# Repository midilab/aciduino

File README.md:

# Aciduino

The DIY Arduino-based Roland TB303 and TR808 Step Sequencer clone and MIDI Controller. Designed using readily available, inexpensive parts. It can be easily assembled on a protoboard or [ordered as PCB](https://pushermanproductions.com/product/midilab-aciduino-303-style-midi-sequencer-pcb-only/). 

There are two flavors of aciduino, the [first version(v1)](https://github.com/midilab/aciduino/tree/master/v1/) is a TB303 sequencer only, the [second version(v2)](https://github.com/midilab/aciduino/tree/master/v2/) is a TB303 and TR808 sequencer with oled display and step/pattern/mute grid system.

Find out more about at [official home page](https://midilab.co/aciduino/)

## [Aciduino V1](https://github.com/midilab/aciduino/tree/master/v1/)  
2 Tracks TB303 sequencer and MIDI Controller.

V1 on PCB

## [Aciduino V2](https://github.com/midilab/aciduino/tree/master/v2/)  
Up to 16 Tracks TB303/TR808 sequencer with step, pattern and mute automation grid system, MIDI Controller, OLED display and extensible modular design to plug more potentiometers, buttons, MIDI or CV/Gate interfaces.

V2 on Protoboard

V2 on PCB(prototype)

Features
========

### 303/808 Step Sequencer clone

Programming bass and drum steps using same analogy of original machines • Save your pattern work on microcontroller EPPROM memory for later live gigs • Use step length and shift to make some unusual sequences • Automation grid system for step edit, pattern navigation and mute tracks • Realtime and Step record modes for MIDI keyboard input(v2 only)

### Professional grade Clock

Tight and solid clock system using hardware timers to achieve realtime professional grade tick system • Send or receive clock to keep all your external equipment synced

### Generative Engine

Generate new and fresh acid music patterns by pressing a single button and twist some parameters • Harmonizer to force musical harmonic modes for bass lines • Euclidian generator for drum parts

### Midi Controller

Controls up to 16 parameters per track of your external synthesizers(bass/drums) • Midi learn(v2 only) • 16 potentiometers modular support to extend aciduino as midi controller(v2 only)

### Pattern memory

Store your patterns conveniently on the microcontroller's EEPROM, allowing you to access them effortlessly during live performances.

# Easy and fast Assembly

1 or 2 hours assembly time on protoboard. 

[V1 Assembly](https://github.com/midilab/aciduino/tree/master/v1)

[V2 Assembly](https://github.com/midilab/aciduino/tree/master/v2#assembly)

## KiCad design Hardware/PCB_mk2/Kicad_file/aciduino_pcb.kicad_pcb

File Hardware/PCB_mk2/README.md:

# ACIDUINO PCB MK2
### <span style="color: red; ">ACIDUINO has been upgraded to MK2 with MIDIinput!</span>
I have created a PCB that can build an aciduino by midilab as a bare board device.
It would be easy to build with less number parts!
Please refer to the folder hierarchy above for the code.
(Be sure to use the latest firmware!)

↓↓↓Completed build image↓↓↓

# About Fabrication
You can get the PCB by submitting the "aciduino_gerber.zip" to a PCB fabrication company in China.
It's usually a lot of 5 pieces.

# BOM List

* 1x arduino nano
* 10x 220ohms resistors
* 1x 4.7kohms resistors
* 1x 1N4148 diodes
* 1x 6N138 optocoupler
* 6x Key switches(If you don't like that, you can substitute a 6mm taticle switch)
* 6x 3mm diffused leds
* 4x 10k linear potentiometers
* 2xMIDI Connector[like this](http://modularanalog.com/?product=midi-jack-5-pin-din-pcb-mount)

!! Additional !!
- A hole is provided to connect a 9V battery box.
- It also works with power supplied from the Arduino's USB port.
- DEMO with my modular and polyend traker(use as MIDI master)[instagram](https://www.instagram.com/reel/CaJfxwNDVI4/?utm_source=ig_web_copy_link)

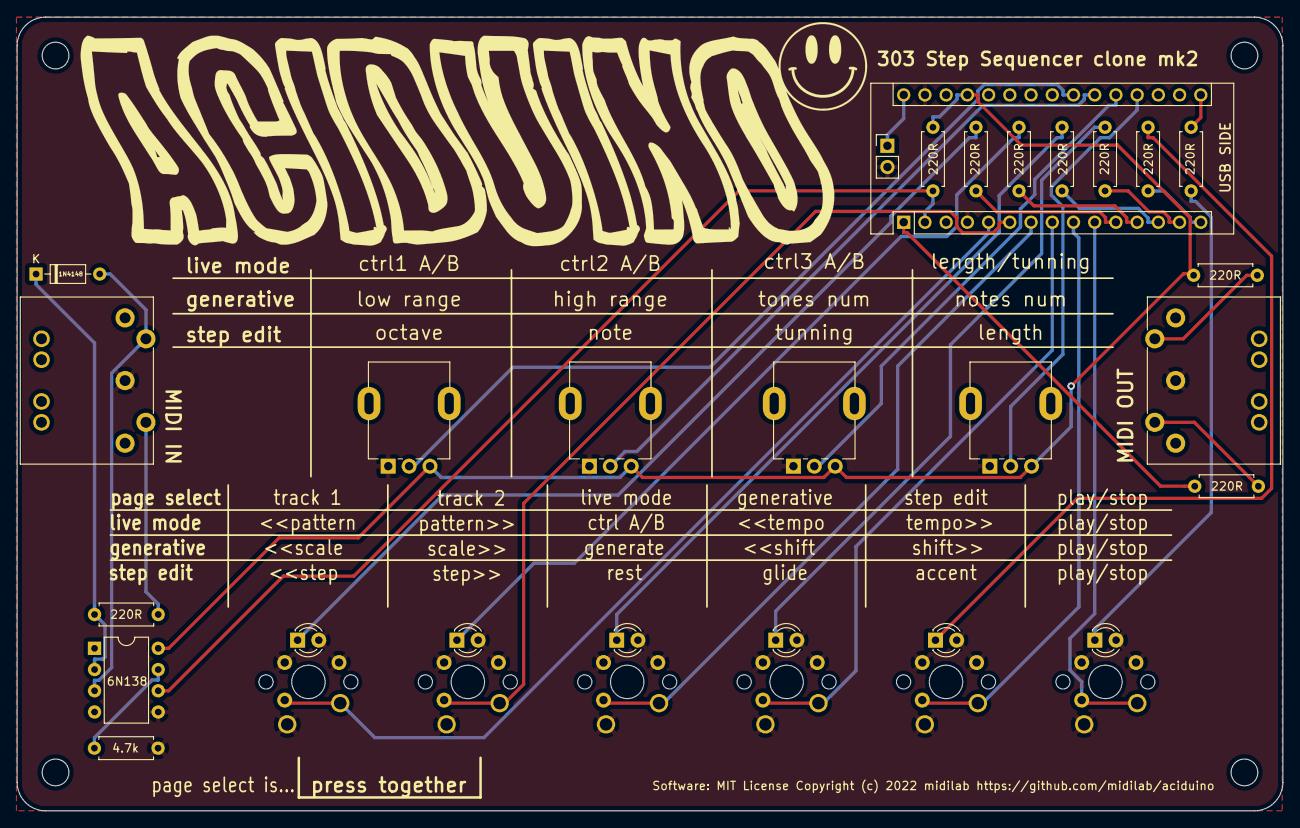
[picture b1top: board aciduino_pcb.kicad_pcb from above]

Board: 2 copper layers, 151.5 x 95.0 mm, 37 parts (0 on the bottom side), 33 nets.

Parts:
A1: Arduino_Nano_v3.x; Arduino_Nano
D1, D2, D3, D4, D5, D6: LED; LED_D3.0mm
D7: 1N4148; D_DO-35_SOD27_P7.62mm_Horizontal
J1: MIDI_OUT; SDS-50J
J2: battery; PinHeader_1x02_P2.54mm_Vertical
J3: MIDI_IN; SDS-50J
R1, R2, R3, R4, R5, R6, R7, R8, R9, R10: 220R; R_Axial_DIN0207_L6.3mm_D2.5mm_P7.62mm_Horizontal
R11: 4.7k; R_Axial_DIN0207_L6.3mm_D2.5mm_P7.62mm_Horizontal
RV1, RV2, RV3, RV4: 10k; Potentiometer_Alpha_RD901F-40-00D_Single_Vertical
SW1, SW2, SW3, SW4, SW5, SW6: SW_Cherry_MX_1.00u_PCB; SW_Cherry_MX_tact_Dual
U1: 6N138; DIP-8_W7.62mm
mount1, mount2, mount3, mount4: Hole_2.2mm; MountingHole_2.2mm_M2_Pad

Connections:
5V: A1.27, R1.1, R10.2, RV1.3, RV2.3, RV3.3, RV4.3, U1.8
9V: A1.30, J2.1
Accent: A1.9, SW5.2
BPM: A1.19, RV4.2
GND: A1.4, A1.29, D1.2, D2.2, D3.2, D4.2, D5.2, D6.2, J1.2, J2.2, J3.2, R11.1, RV1.1, RV2.1, RV3.1, RV4.1, SW1.1, SW2.1, SW3.1, SW4.1, SW5.1, SW6.1, U1.5
Glide: A1.8, SW4.2
LED1: A1.11, R3.1
LED2: A1.12, R4.1
LED3: A1.13, R5.1
LED4: A1.14, R6.1
LED5: A1.15, R7.1
LED6: A1.16, R8.1
Length: A1.20, RV3.2
MIDI_IN: A1.2, R10.1, U1.6
MIDI_OUT: A1.1, R2.2
unnamed: D1.1, R3.2
unnamed: D2.1, R4.2
unnamed: D3.1, R5.2
unnamed: D4.1, R6.2
unnamed: D5.1, R7.2
unnamed: D6.1, R8.2
unnamed: D7.1, R9.1, U1.2
unnamed: D7.2, J3.5, U1.3
unnamed: J1.4, R1.2
unnamed: J1.5, R2.1
unnamed: J3.4, R9.2
unnamed: R11.2, U1.7
Next_STEP: A1.6, SW2.2
Note: A1.21, RV2.2
Octave: A1.22, RV1.2
PLAY_STOP: A1.10, SW6.2
Prev_STEP: A1.5, SW1.2
Rest: A1.7, SW3.2

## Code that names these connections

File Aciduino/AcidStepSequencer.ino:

// Acid StepSequencer, a Roland TB303 step sequencer engine clone
// author: midilab contact@midilab.co
// under MIT license
#include "uClock.h"

#define NOTE_STACK_SIZE    3

// MIDI clock, start, stop, note on and note off byte definitions - based on MIDI 1.0 Standards.
#define MIDI_CLOCK 0xF8
#define MIDI_START 0xFA
#define MIDI_STOP  0xFC
#define NOTE_ON    0x90
#define NOTE_OFF   0x80
#define MIDI_CC    0xB0

// sequencer data
typedef struct
{
  uint8_t note;
  int16_t length;
} STACK_NOTE_DATA;

typedef struct
{
  uint8_t note:7;
  uint8_t accent:1;
  uint8_t glide:1;
  uint8_t rest:1;
  uint8_t reserved:6;
} SEQUENCER_STEP_DATA;
// 2 bytes per step

typedef struct
{
  SEQUENCER_STEP_DATA step[STEP_MAX_SIZE];
  int8_t step_init_point;
  uint8_t step_length;
} SEQUENCER_TRACK_DATA;
// 32 bytes per 16 step + 2 bytes config = 34 bytes [STEP_MAX_SIZE=16]

typedef struct
{
  SEQUENCER_TRACK_DATA data;
  uint8_t step_location;
  uint8_t channel;
  bool mute;
  STACK_NOTE_DATA stack[NOTE_STACK_SIZE];  
} SEQUENCER_TRACK;

// main sequencer data is constantly change inside uClock 16PPQN and 96PPQN ISR callbacks, so volatile him!
SEQUENCER_TRACK volatile _sequencer[TRACK_NUMBER];

uint8_t _selected_track = 0;
uint8_t _selected_pattern = 0;

// make sure all above sequencer data are modified atomicly only
// eg. ATOMIC(_sequencer[track]data.step[0].accent = 1); ATOMIC(_sequencer[track].data.step_length = 7);

// shared data to be used for user interface interaction and feedback
bool _playing = false;
uint8_t _harmonize = 0;
uint16_t _step_edit = 0;
uint8_t _last_octave = 3;
uint8_t _last_note = 0;
int8_t _transpose = 0; // zero is centered C
uint8_t _selected_mode = 0;

void sendMidiMessage(uint8_t command, uint8_t byte1, uint8_t byte2, uint8_t channel)
{   
  // send midi message
  command = command | (uint8_t)channel; 
  Serial.write(command);
  Serial.write(byte1);
  Serial.write(byte2);
}

// The callback function wich will be called by uClock each Pulse of 16PPQN clock resolution. Each call represents exactly one step.
void ClockOut16PPQN(uint32_t * tick) 
{
  uint8_t step;
  uint16_t length;
  int8_t note;

  for ( uint8_t track = 0; track < TRACK_NUMBER; track++ ) {

    if ( _sequencer[track].mute == true ) {
      continue;
    }
    
    length = NOTE_LENGTH;
    
    // get actual step location.
    _sequencer[track].step_location = uint32_t(*tick + _sequencer[track].data.step_init_point) % _sequencer[track].data.step_length;
    
    // send note on only if this step are not in rest mode
    if ( _sequencer[track].data.step[_sequencer[track].step_location].rest == 0 ) {
  
      // check for glide event ahead of _sequencer[track].step_location
      step = _sequencer[track].step_location;
      for ( uint8_t i = 1; i < _sequencer[track].data.step_length; i++  ) {
        ++step;
        step = step % _sequencer[track].data.step_length;
        if ( _sequencer[track].data.step[step].glide == 1 && _sequencer[track].data.step[step].rest == 1 ) {
          length = NOTE_LENGTH + (i * 6);
          break;
        } else if ( _sequencer[track].data.step[step].rest == 0 ) {
          break;
        }
      }
  
      // find a free note stack to fit in
      for ( uint8_t i = 0; i < NOTE_STACK_SIZE; i++ ) {
        if ( _sequencer[track].stack[i].length == -1 ) {
          if ( _harmonize == 1 ) {
            note = harmonizer(_sequencer[track].data.step[_sequencer[track].step_location].note);
          } else {
            note = _sequencer[track].data.step[_sequencer[track].step_location].note;
          }
          note += _transpose;
          // in case transpose push note away from the lower or higher midi note range barrier do not play it
          if ( note < 0 || note > 127 ) {
            break;
          }
          _sequencer[track].stack[i].note = note;
          _sequencer[track].stack[i].length = length;
          // send note on
          sendMidiMessage(NOTE_ON, note, _sequencer[track].data.step[_sequencer[track].step_location].accent ? ACCENT_VELOCITY : NOTE_VELOCITY, _sequencer[track].channel);    
          break;
        }
      }
      
    } 
    
  } 
  
}

void clearStackNote(int8_t track = -1)
{
  if ( track <= -1 ) {
    // clear all tracks stack note
    for ( uint8_t i = 0; i < TRACK_NUMBER; i++ ) {
      // clear and send any note off 
      for ( uint8_t j = 0; j < NOTE_STACK_SIZE; j++ ) {
        ATOMIC(
          sendMidiMessage(NOTE_OFF, _sequencer[i].stack[j].note, 0, _sequencer[i].channel);
          _sequencer[i].stack[j].length = -1;
        )
      } 
    }
  } else {
    // clear and send any note off 
    for ( uint8_t i = 0; i < NOTE_STACK_SIZE; i++ ) {
      ATOMIC(
        sendMidiMessage(NOTE_OFF, _sequencer[track].stack[i].note, 0, _sequencer[track].channel);
        _sequencer[track].stack[i].length = -1;
      )
    }     
  }

}

// The callback function wich will be called by uClock each Pulse of 96PPQN clock resolution.
void ClockOut96PPQN(uint32_t * tick) 
{
  uint8_t track;
    
  // Send MIDI_CLOCK to external hardware
  Serial.write(MIDI_CLOCK);

  for ( track = 0; track < TRACK_NUMBER; track++ ) {

    // handle note on stack
    for ( uint8_t i = 0; i < NOTE_STACK_SIZE; i++ ) {
      if ( _sequencer[track].stack[i].length != -1 ) {
        --_sequencer[track].stack[i].length;
        if ( _sequencer[track].stack[i].length == 0 ) {
          sendMidiMessage(NOTE_OFF, _sequencer[track].stack[i].note, 0, _sequencer[track].channel);
          _sequencer[track].stack[i].length = -1;
        }
      }  
    }
  
  }
  
  // user feedback about sequence time events
  tempoInterface(tick);
}

// The callback function wich will be called when clock starts by using Clock.start() method.
void onClockStart() 
{
  Serial.write(MIDI_START);
  _playing = 1;
}

// The callback function wich will be called when clock stops by using Clock.stop() method.
void onClockStop() 
{
  Serial.write(MIDI_STOP);

  // clear all tracks stack note
  clearStackNote();
    
  _playing = 0;
}

void setTrackChannel(uint8_t track, uint8_t channel) 
{
  --track;
  --channel;
  ATOMIC(_sequencer[track].channel = channel);
}

void initAcidStepSequencer(uint8_t mode)
{
  uint8_t track;
  
  // Initialize serial communication
  if ( mode == 0 ) {
    // the default MIDI serial speed communication at 31250 bits per second
    Serial.begin(31250);
  } else if ( mode == 1 ) {
    // for usage with a PC with a serial to MIDI bridge
    Serial.begin(115200);
  }

  // Inits the clock
  uClock.init();
  
  // Set the callback function for the clock output to send MIDI Sync message.
  uClock.setClock96PPQNOutput(ClockOut96PPQN);
  
  // Set the callback function for the step sequencer on 16ppqn
  uClock.setClock16PPQNOutput(ClockOut16PPQN);  
  
  // Set the callback function for MIDI Start and Stop messages.
  uClock.setOnClockStartOutput(onClockStart);  
  uClock.setOnClockStopOutput(onClockStop);
  
  // Set the clock BPM to 126 BPM
  uClock.setTempo(126);

  // initing sequencer memory data
  for ( track = 0; track < TRACK_NUMBER; track++ ) {

    _sequencer[track].channel = track;
    _sequencer[track].data.step_init_point = 0;
    _sequencer[track].data.step_length = STEP_MAX_SIZE;
    _sequencer[track].step_location = 0;
    _sequencer[track].mute = false;

    // initing note data
    for ( uint16_t i = 0; i < STEP_MAX_SIZE; i++ ) {
      _sequencer[track].data.step[i].note = 48;
      _sequencer[track].data.step[i].accent = 0;
      _sequencer[track].data.step[i].glide = 0;
      _sequencer[track].data.step[i].rest = 0;
    }
  
    // initing note stack data
    for ( uint8_t i = 0; i < NOTE_STACK_SIZE; i++ ) {
      _sequencer[track].stack[i].note = 0;
      _sequencer[track].stack[i].length = -1;
    }
    
  }
  
}

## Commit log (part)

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2018-03-10 Inital commit, kinda of fork from a simple exampla of uClock usage to a bigger project with more features.
2018-03-12 Adding gitattributes to setup all .ino as language C
2018-03-14 Added Fritzing file as main hardware development platform. Directory structure to separate Software and Hardware.
2018-03-14 Better config organization to easily create new interfaces for sequencer core.
2018-03-19 Hotfix: Initializing length variable on step handler to avoid long gosth notes.
2018-04-09 Added uClock library v0.8 locally to get life of DIYers easier for compile.
2018-04-09 Change README to reflect changes on uClock library dependency
2018-04-11 Added features
2018-04-12 2 tracks support added, 3 pages added, partially generative implemented. no controller page yet.
2018-04-12 Fix: Stable Harmonizer
2018-04-12 Generative interface changes, Controller interface changes. Check README.md for more info.
2018-04-12 Created a config.h to centralize all user side hacks config.
2018-04-15 Hotfix: _transpose, _harmonize and _selected_mode are now acced atomiclly to avoid race conditions between main code and ISR code. Brief Manual notes added for pages.
2018-04-15 Manual complement on README.md
2018-04-16 Added project BOM List
2018-04-16 README.md markup fix
2018-07-16 uClock library updated to newest version. It has some hotfixes related to external slave gear sync. Please check https://github.com/midilab/uClock/ for more detailed info.
2018-10-26 Hotfix: Midi controller screw clock timming while send CC data like crazy on bad breadboard with bad potentiometers, raise it and add a config option to set it on config.h
2018-11-07 pre 1.1 release. changelog: live mode page - prepared to comming save and load pattern, plus most used live commands to acidulize your self generative page - 2 new genarative parameters: number of to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
2018-11-07 hotfixes for 1.1 pre release: - read all pots at boot to avoid firts read problems with real data command - restrict max_value on getPotChanges()
2018-11-09 Hotfix: more stable version of holded() for button hold action
2018-11-09 visual feedback status for save and clear pattern on eeprom memory. hotfix for last pattern loaded on non existent pattern slot
2018-11-10 Manual usage update on readme.
2018-11-10 Manual usage update on readme. markup fixes 2
2018-11-10 Improvement: add user a config.h option USE_MIDI_CTRL to be set to true or false to enbale or disable usage of midi controler cc messages
2020-08-21 no need for drift setup on aciduino arduino nano.
2020-08-21 uclock v0.8.3 updated
2021-08-08 AddPCBdata
2021-08-10 addPCB
2022-02-23 Update PCB
2022-02-24 Update gerber
2022-02-27 fix README.md images path
2022-02-27 added ijnekenamay's PCB reference
2022-03-01 added slave midi input sync code support
2022-04-03 fix warning about ATOMIC defined twice. keep only the uClock one
2022-06-15 Add Kicad file
2022-09-26 finished generative engine, added bjorklund as randomizer option. work in progress
2022-09-26 fix engine output midi data
2022-09-27 finished generative ui components. work in progress...
2022-09-28 get ride off uctrl midi implementation to flash memory, get our own simple implementation for this project
2022-09-28 added basic midi control setup for live page + midi cc mapping data for tb303, tr808 and tr909 from roland cloud manuals
2022-10-03 midi controller object for 303 and 808 roland cloud
2022-10-03 set uclock to a release v1.1.2
2022-10-03 set uclock to a release v1.1.3
2022-10-03 add fritzing initial breadboard and components
2022-10-05 added a png for schematics on breadboard. changes on UI/UX after some tests
2022-10-06 better ui/ux for navigation selection
2022-10-07 add global accent as option for 808
2022-10-07 added basic roll/substep to 808 engine
2022-10-11 added tie support for 303 and slide fix for 3030 engine
2022-10-14 added clear track, simplifier navigation, dedicated shift+page1 button for tempo setup
2022-10-15 move things around for release
2022-10-15 added tie support.
2022-10-17 added support for midi uart
2022-10-18 fullscreen view of step sequencer
2022-10-18 added aciduino breadboard schematic png for faster view
2022-10-29 step sequencer full view navigation done
2022-10-30 -reoganize repo for v1 and v2. -added uCtrl as submodule. -normalize tap function send note
2022-10-30 Revert "added v2 lite assembly photos" Photos way too large!
    This reverts commit f0e6f4ddabd4587a42cf8622a7c083973dd9fcf0.
2022-10-31 added mute feature
2022-11-01 how to use basics for v2
2022-11-01 formating readme
2022-11-01 change readme images path references for master branch
2022-11-01 fix readme paths
2022-11-03 fix assembly exaplanation reference for pot base placement
2022-11-03 update notes
2022-11-08 fix slide behaviour or 303 engine
2022-11-08 fix slide/tie event
2022-11-09 simplified change interface for pagecomponent, now it can handle secondary and pot as changers
2022-11-09 added 303 octave/note control behaviour
2022-11-10 fix submodule uClock
2022-11-10 fix octave object change by inc/dec
2022-11-16 MidiCCControl goes to heap for initial setup of track size handling to avoid index crashes
2022-11-29 rewrite MidiCCControl component for better memory footprint. Added new midi cc for 808 and 303
2022-11-29 set live page to 1 subpage for now until pattern driven mute ready
2022-12-01 add step sequencer pot/shift+pot controls manual reference
2022-12-01 fix missbehaviour of update_selector on step page
2022-12-09 added mute pattern component for live page
2022-12-19 update ijnekenamay's pcb for new tie event panel title
2022-12-21 added avr mega 2560 support
2022-12-22 fix numbering display on avr
2022-12-22 added uCtrl midi module support for easy multi-platform ports and hadling
2022-12-25 experimental support for esp32 wroom boards
2022-12-26 non working version of esp32, still experimental, needs some review for multithread enviroment
2022-12-29 experimental version of esp32
2023-01-02 added UI step sequencer grid support for 256 steps on 303 engines
2023-01-04 change README notes
2023-01-06 uCtrl update for ain 4051 fix
2023-01-06 added basic support for 16 pots midi controller via ain driver(using 2x 4051)
2023-01-06 fix pot16 direct access midi controller
2023-01-06 add pot16 schematic for aciduino v2 16 potentiometer midi controler extension
2023-01-09 ESP32 new wiring setup
2023-01-09 update uCtrl library
2023-01-25 update uCtrl to latest
2023-01-25 raise for 4x 303 as default
2023-01-25 added new pages syst(system setup), midi, pattern
2023-01-25 fix load pattern from epprom
2023-01-26 change save pattern behaviour. fix grid size for session and system components
2023-01-26 add auto load session and first slot pattern from epprom at boot
2023-01-27 move POT16 proc out of ISR to avoid locks on notes
2023-01-27 update uCtrl back for ain isr
2023-01-29 realtime midi record
2023-02-04 update uCtrl
2023-02-04 added pattern grid support with epprom save/load and copy/paste feature
2023-02-06 fix action hook and din shiftregisters+pins indexing ports
2023-02-06 added dedicated transport button as an build option
2023-02-06 fill all 16 CCs for 303
2023-02-06 UI changes for page actions
2023-02-06 release candidate updates
2023-08-05 updating uCtrl
2023-08-05 fix esp32 compilation
2023-08-30 add reference for v2 release pack download
2023-08-31 off by 1 button assign bugfix
2023-08-31 fix uCtrl new version api usage
2023-09-02 fix ain callback usage on hardware init
2023-09-03 fix off-by-one bug on pot changer.
2023-09-03 update uCtrl and uClock versions
2023-09-05 uClock update to support esp32
2023-09-05 uCtrl update to support esp32
2023-09-05 esp32 support added with midi sync!
2023-09-12 added esp32 usb-midi native support(experimental)
2023-09-12 update uCtrl to fix esp32 native usb midi compile
2023-09-21 update uClock version to new shuffle support
2023-09-22 fix shuffle edge case for +5 ticks
2023-09-22 fix shuffle edge case for -5 ticks
2023-10-18 fix esp32 usb midi freezing
2023-10-31 config for B_A_T
    changed pins
    changed display orientation
    changed ptrn length
    removed examples
2023-10-31 added doc folder images
    starting a user manual
2023-10-31 changed seqr images
2023-11-02 merged subpages images
    one img for each page, no more img / subpage
2023-11-02 seqr update
    descirption seqr
2023-11-02 Update ACIDUINO V2 MIDI Sequencer USER Manual.md
    test from webpage
2023-12-10 chore: added ports section to src/ clean way of create or change a port
2023-12-10 fix: page memory initialize before start operation
2023-12-11 remove modules.h requirement for ain
2023-12-13 organize ports data and uCtrl version
2023-12-14 Revert back 0_hardware_setup.ino
2023-12-14 Revert Back setup.h
2023-12-18 wip: new esp32 extension module
2023-12-18 feature: new wroom-ext1.h port
2023-12-18 fix: update uCtrl for esp32 adc max resolution support
2023-12-19 update README for breakchanges
2023-12-19 fix wroom pinout for pot control
2023-12-21 improvment: keep testing, fix and review esp32 implementation
2023-12-23 fix: interruped setup for midi call
2023-12-23 fix: wrongly commited Serial.begin for debug
2024-01-05 porting aciduino to new uctrl and uclock version. supports ble midi out of the box for esp32
2024-01-05 getting uCtrl back to main branch after pullrequest for ble midi
2024-01-05 uCtrl update
2024-01-06 restore shuffle back with 7 templates, based on 909 and mpc60
2024-01-06 shuffle fix along with new uClock release 2.0
2024-01-06 fix: roll and shuffle based on new uClock v2
2024-01-06 fix: compile fix in case esp32 wroom dont set bluetooth midi
2024-01-07 chore: update uCtrl and uClock libraries
2024-01-08 external sync revised with new uClock v2
2024-01-27 clean up messy macos DS_Store files and fix uClock submodule version
2024-01-27 rename main doc file to lowercase
2024-02-22 3D printed Case 1.3in added
2024-02-22 3D printed Case 2.4 in 128x64 OLED Version
2024-05-22 wip: cleanup and organize sequencer and ui components
2024-05-23 added raw interface entrypoints and uCtrl update that supports a loopCallback function
2024-05-23 example usage for raw interface schema
2024-05-26 encapsulated track output setup memory access
2024-05-26 wip: partial midi control encapsulation
2024-06-04 ported mute_grid memory schema into aciduino class
2024-06-04 ported pattern grid memory into aciduino class. fixing compile issues and code reorg
2024-06-05 finishing code encapsulation for aciduino class separation with interfaces and hardware setup
2024-06-05 added some realcode example for raw interface to deal with aciduino sequencer
2024-06-05 fix callback playing status integration with uclock and aciduino
2024-06-05 fix raw interface example for compile
2024-06-06 fix off-by-one din id for step on/off
2024-06-06 fix esp32 -fpermise compilation errors and port esp32 ports to new aciduino schema
2024-06-06 finishing whole code encapsulation port. missing tests
2024-06-06 fix generative accent and fill for 303 param change
2024-06-06 remove unsed macros on ports
2024-06-11 update uCtrl to main branch over v1.2 release
2024-06-23 README notes update
2024-11-16 - set develop entrypoints for uClock and uCtrl for wip development
2024-11-16 - update uCtrl version
2025-03-30 update uClock to the latest develop version
2025-07-29 added latest uClock develop version alog with better ext sync and external bpm smooth reads with uClock.setExtIntervalBuffer(32)
2025-07-31 updated uCtrl and uClock to latest develop version. added pause function(wip)
2025-07-31 update latest develop uClock version
2025-07-31 update uClock to latest develop
2025-08-02 new uClock develop with better external sync schema
2025-08-03 updated latest uCtrl and uClock
2025-08-04 updated to latest uClock. fixes on external sync
2025-08-05 update uClock and uCtrl to latest develop version
2025-11-08 update to pre v2.3.0 uClock library

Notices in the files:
Hardware/PCB_mk2/Kicad_file/aciduino_pcb.kicad_pcb:
Hardware: OpenSourceHardware Copyright(c) 2022 KenjiYamane https://github.com/ijnekenamay
Software: MIT License Copyright (c) 2022 midilab https://github.com/midilab/aciduino
